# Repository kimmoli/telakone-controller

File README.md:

telakone-controller
===================

STM32F407ZG + CC3100MOD WiFi with external antenna

12V to 3.3V switch mode power supply

Full bridge motor control with current measurement

4x high-side outputs
* PWM capable
* +12V, few amps

Dual isolated eBike motor control
* Throttle control (0-5V output)
* Brake and Reverse (low-side outputs)
* +48V voltage measurement

+12V supply voltage measurement

Temperature sensor

3-Axis accelerometer

Joystick input
* 2 potentiometers
* 2 buttons

Speed sensor inputs
* 2 channels
* for MLX90217 gear tooth sensor

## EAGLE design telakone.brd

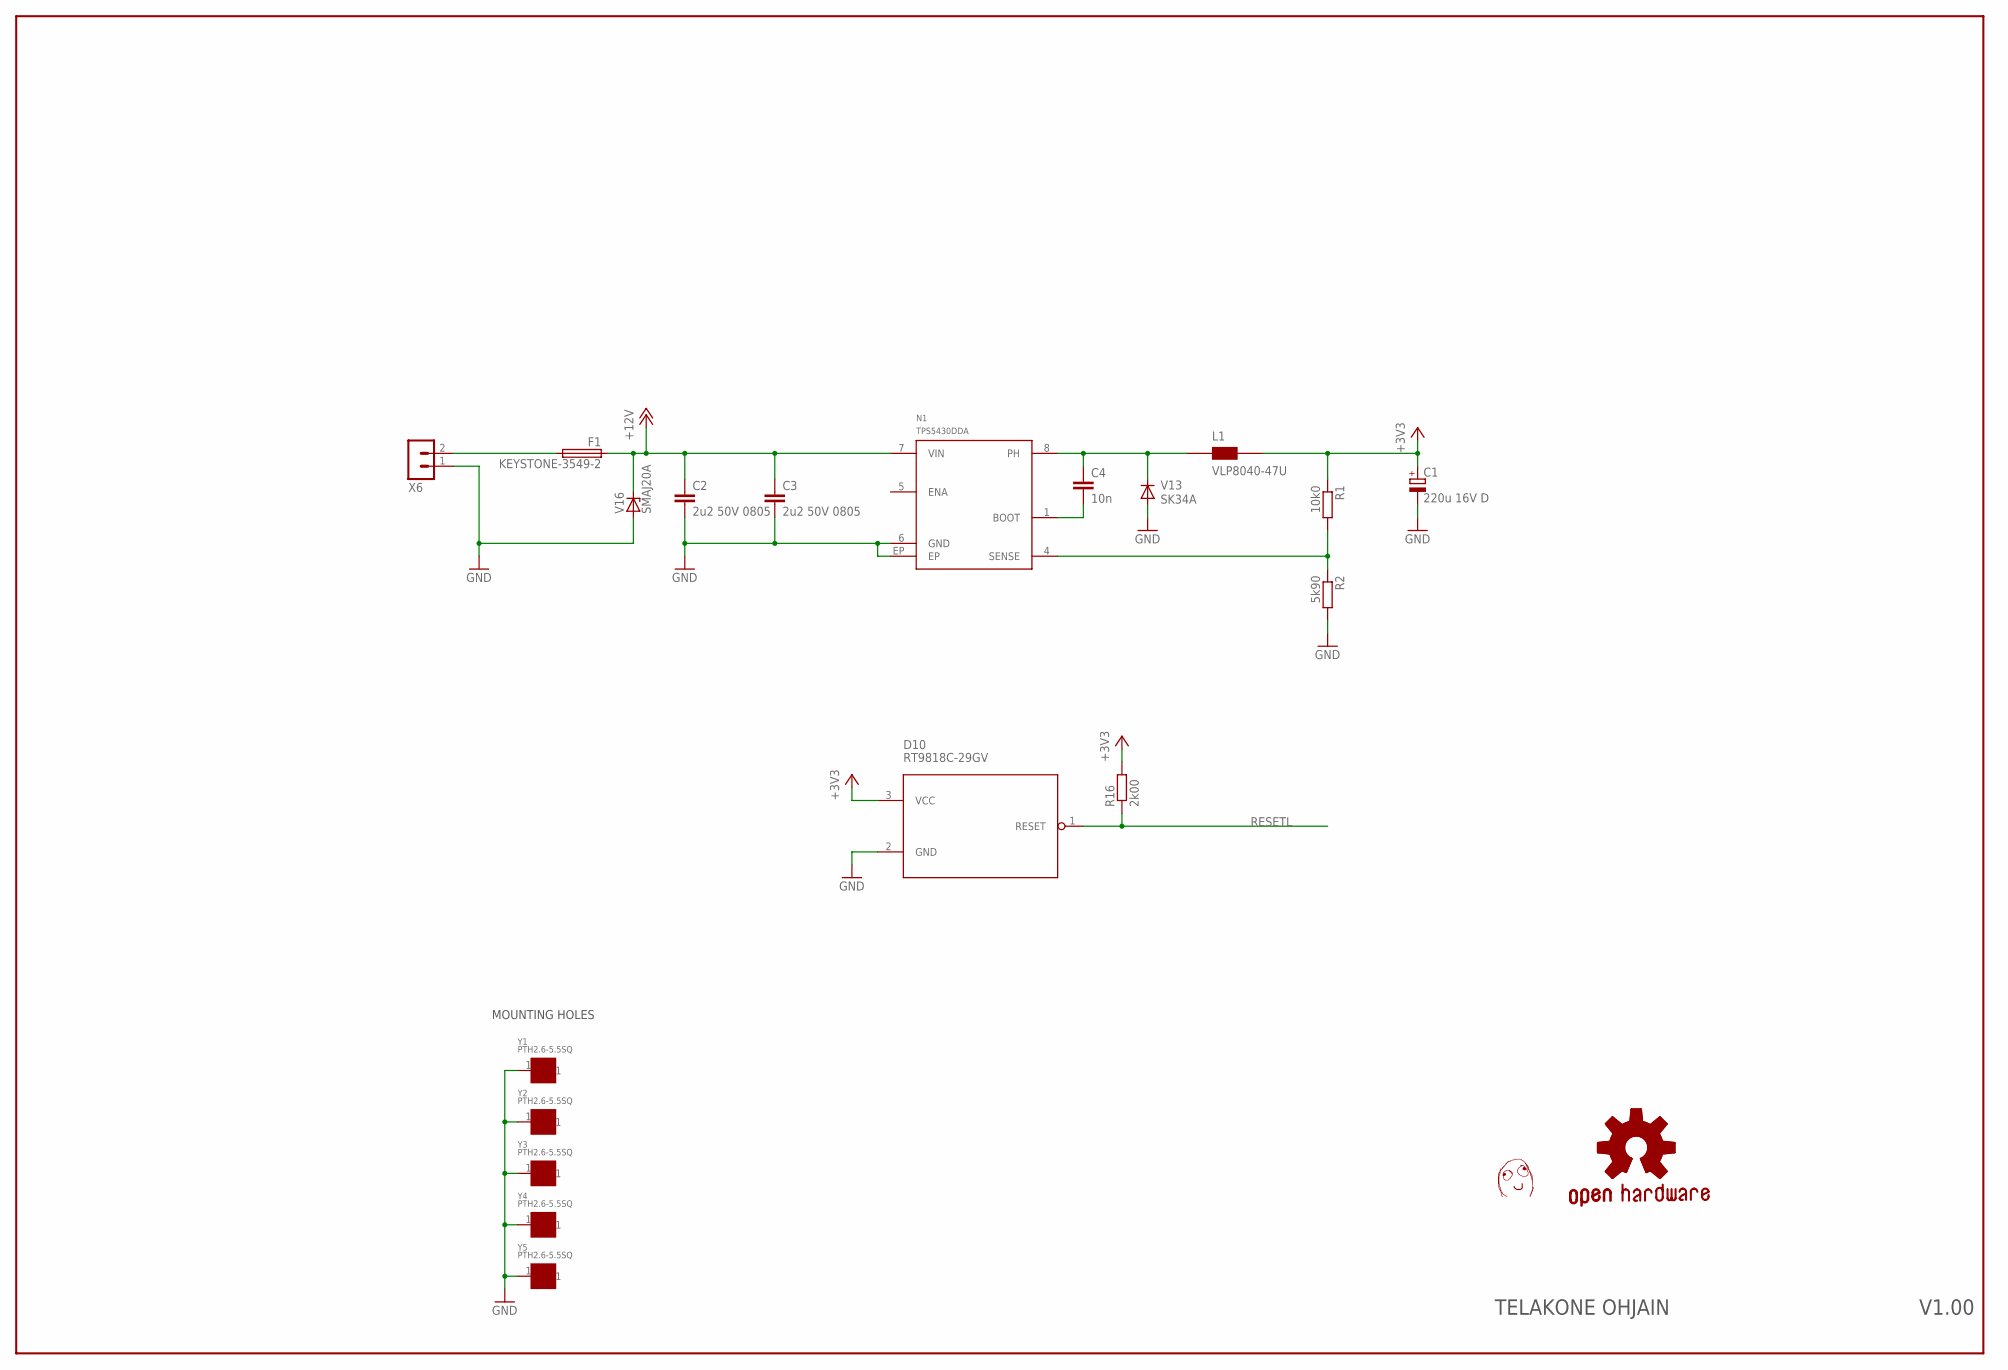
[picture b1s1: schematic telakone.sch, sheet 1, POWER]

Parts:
C1: 220u 16V D; CT7343
C2, C3: 2u2 50V 0805; C0805
C4: 10n; C0603
D10: RT9818C-29GV; SOT23
F1: KEYSTONE-3549-2
L1: VLP8040-47U; VLP8040
N1: TPS5430DDA; SOIC8-N-EP
R1: 10k0; R0603
R2: 5k90; R0603
R16: 2k00; R0603
U$1: DAFUG
V13: SK34A; DO214AC
V16: SMAJ20A; DO214AC
X6: TE_RUUVILIITIN2
Y1, Y2, Y3, Y4, Y5: PTH2.6-5.5SQ; PTH-2.6-5.5SQ

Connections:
+3V3: C1.+, D10.3 (VCC), L1.2 (B), R1.1, R16.2; also elsewhere on the board
+12V: C2.1, C3.1, F1.1, F1.4 (1), N1.7 (VIN), V16.C; also elsewhere on the board
GND: C1.-, C2.2, C3.2, D10.2 (GND), N1.6 (GND), N1.EP, R2.2, V13.A, V16.A, X6.1, Y1.1, Y2.1, Y3.1, Y4.1, Y5.1; also elsewhere on the board
unnamed: C4.1, L1.1 (A), N1.8 (PH), V13.C
unnamed: C4.2, N1.1 (BOOT)
unnamed: N1.4 (SENSE), R1.2, R2.1
unnamed: F1.2, F1.3 (2), X6.2
RESETL: D10.1 (RESET), R16.1; also elsewhere on the board

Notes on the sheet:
MOUNTING HOLES
V1.00
TELAKONE OHJAIN

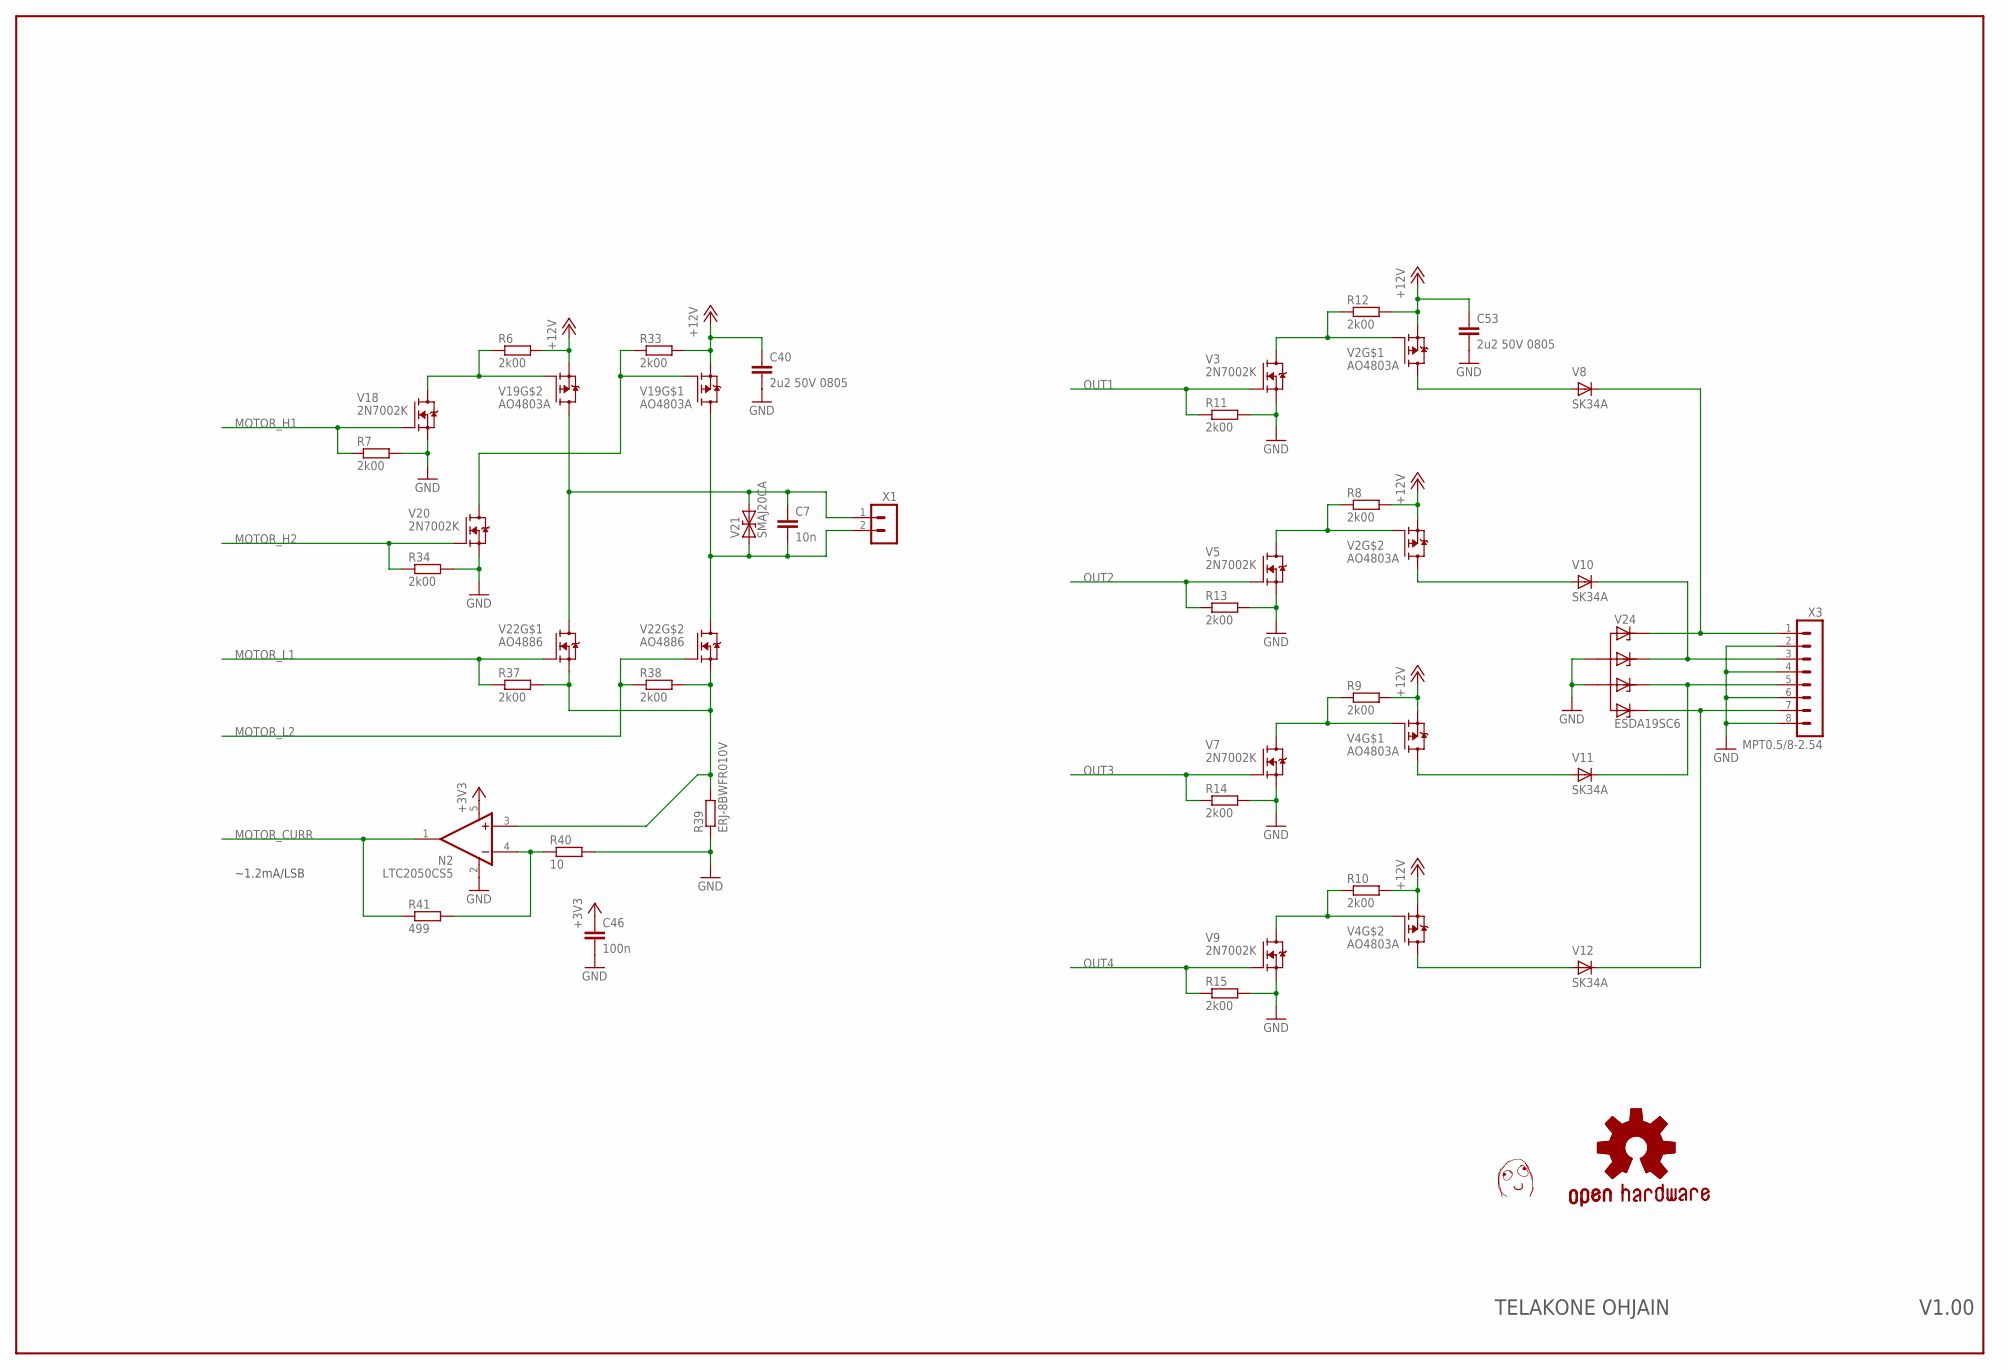
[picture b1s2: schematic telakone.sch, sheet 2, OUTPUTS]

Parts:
C7: 10n; C0603
C40, C53: 2u2 50V 0805; C0805
C46: 100n; C0603
N2: LTC2050CS5; SOT95P280X145-5N
R6, R7, R8, R9, R10, R11, R12, R13, R14, R15, R33, R34, R37, R38: 2k00; R0603
R39: ERJ-8BWFR010V; R1206
R40: 10; R0603
R41: 499; R0603
U$3: DAFUG
V2, V4, V19: AO4803A; SOIC8-N_MC
V3, V5, V7, V9, V18, V20: 2N7002K; SOT23
V8, V10, V11, V12: SK34A; DO214AC
V21: SMAJ20CA; DO214AC
V22: AO4886; SOIC8-N_MC
V24: ESDA19SC6; SOT23-6
X1: TE_RUUVILIITIN2
X3: MPT0.5/8-2.54

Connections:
+3V3: C46.1, N2.5 (V+); also elsewhere on the board
+12V: C40.1, C53.1, R6.2, R8.2, R9.2, R10.2, R12.2, R33.2, V2.1 (S), V2.3 (S), V4.1 (S), V4.3 (S), V19.1 (S), V19.3 (S); also elsewhere on the board
GND: C40.2, C46.2, C53.2, N2.2 (V-), R7.2, R11.2, R13.2, R14.2, R15.2, R34.2, R39.1, R40.2, V3.2 (S), V5.2 (S), V7.2 (S), V9.2 (S), V18.2 (S), V20.2 (S), V24.2 (A), V24.5 (A1), X3.2, X3.4, X3.6, X3.8; also elsewhere on the board
MOTOR_CURR: N2.1 (OUT), R41.1; also elsewhere on the board
MOTOR_H1: R7.1, V18.1 (G); also elsewhere on the board
MOTOR_H2: R34.1, V20.1 (G); also elsewhere on the board
MOTOR_L1: R37.1, V22.4 (G); also elsewhere on the board
MOTOR_L2: R38.1, V22.2 (G); also elsewhere on the board
unnamed: R6.1, V18.3 (D), V19.2 (G)
unnamed: R33.1, V19.4 (G), V20.3 (D)
unnamed: N2.3 (+IN), R37.2, R38.2, R39.2, V22.1 (S), V22.3 (S)
unnamed: N2.4 (-IN), R40.1, R41.2
unnamed: R8.1, V2.2 (G), V5.3 (D)
unnamed: R12.1, V2.4 (G), V3.3 (D)
unnamed: R9.1, V4.4 (G), V7.3 (D)
unnamed: R10.1, V4.2 (G), V9.3 (D)
unnamed: V12.C, V24.6 (C3), X3.7
unnamed: V11.C, V24.4 (C2), X3.5
unnamed: V10.C, V24.3 (C1), X3.3
unnamed: V8.C, V24.1 (C), X3.1
NERT: V2.5 (D), V2.6 (D), V8.A
NERT1: V2.7 (D), V2.8 (D), V10.A
NERT2: V4.5 (D), V4.6 (D), V11.A
NERT3: V4.7 (D), V4.8 (D), V12.A
NERT4: C7.1, V19.7 (D), V19.8 (D), V21.A (2), V22.5 (D), V22.6 (D), X1.1
NERT5: C7.2, V19.5 (D), V19.6 (D), V21.C (1), V22.7 (D), V22.8 (D), X1.2
OUT1: R11.1, V3.1 (G); also elsewhere on the board
OUT2: R13.1, V5.1 (G); also elsewhere on the board
OUT3: R14.1, V7.1 (G); also elsewhere on the board
OUT4: R15.1, V9.1 (G); also elsewhere on the board

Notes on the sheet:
~1.2mA/LSB
V1.00
TELAKONE OHJAIN

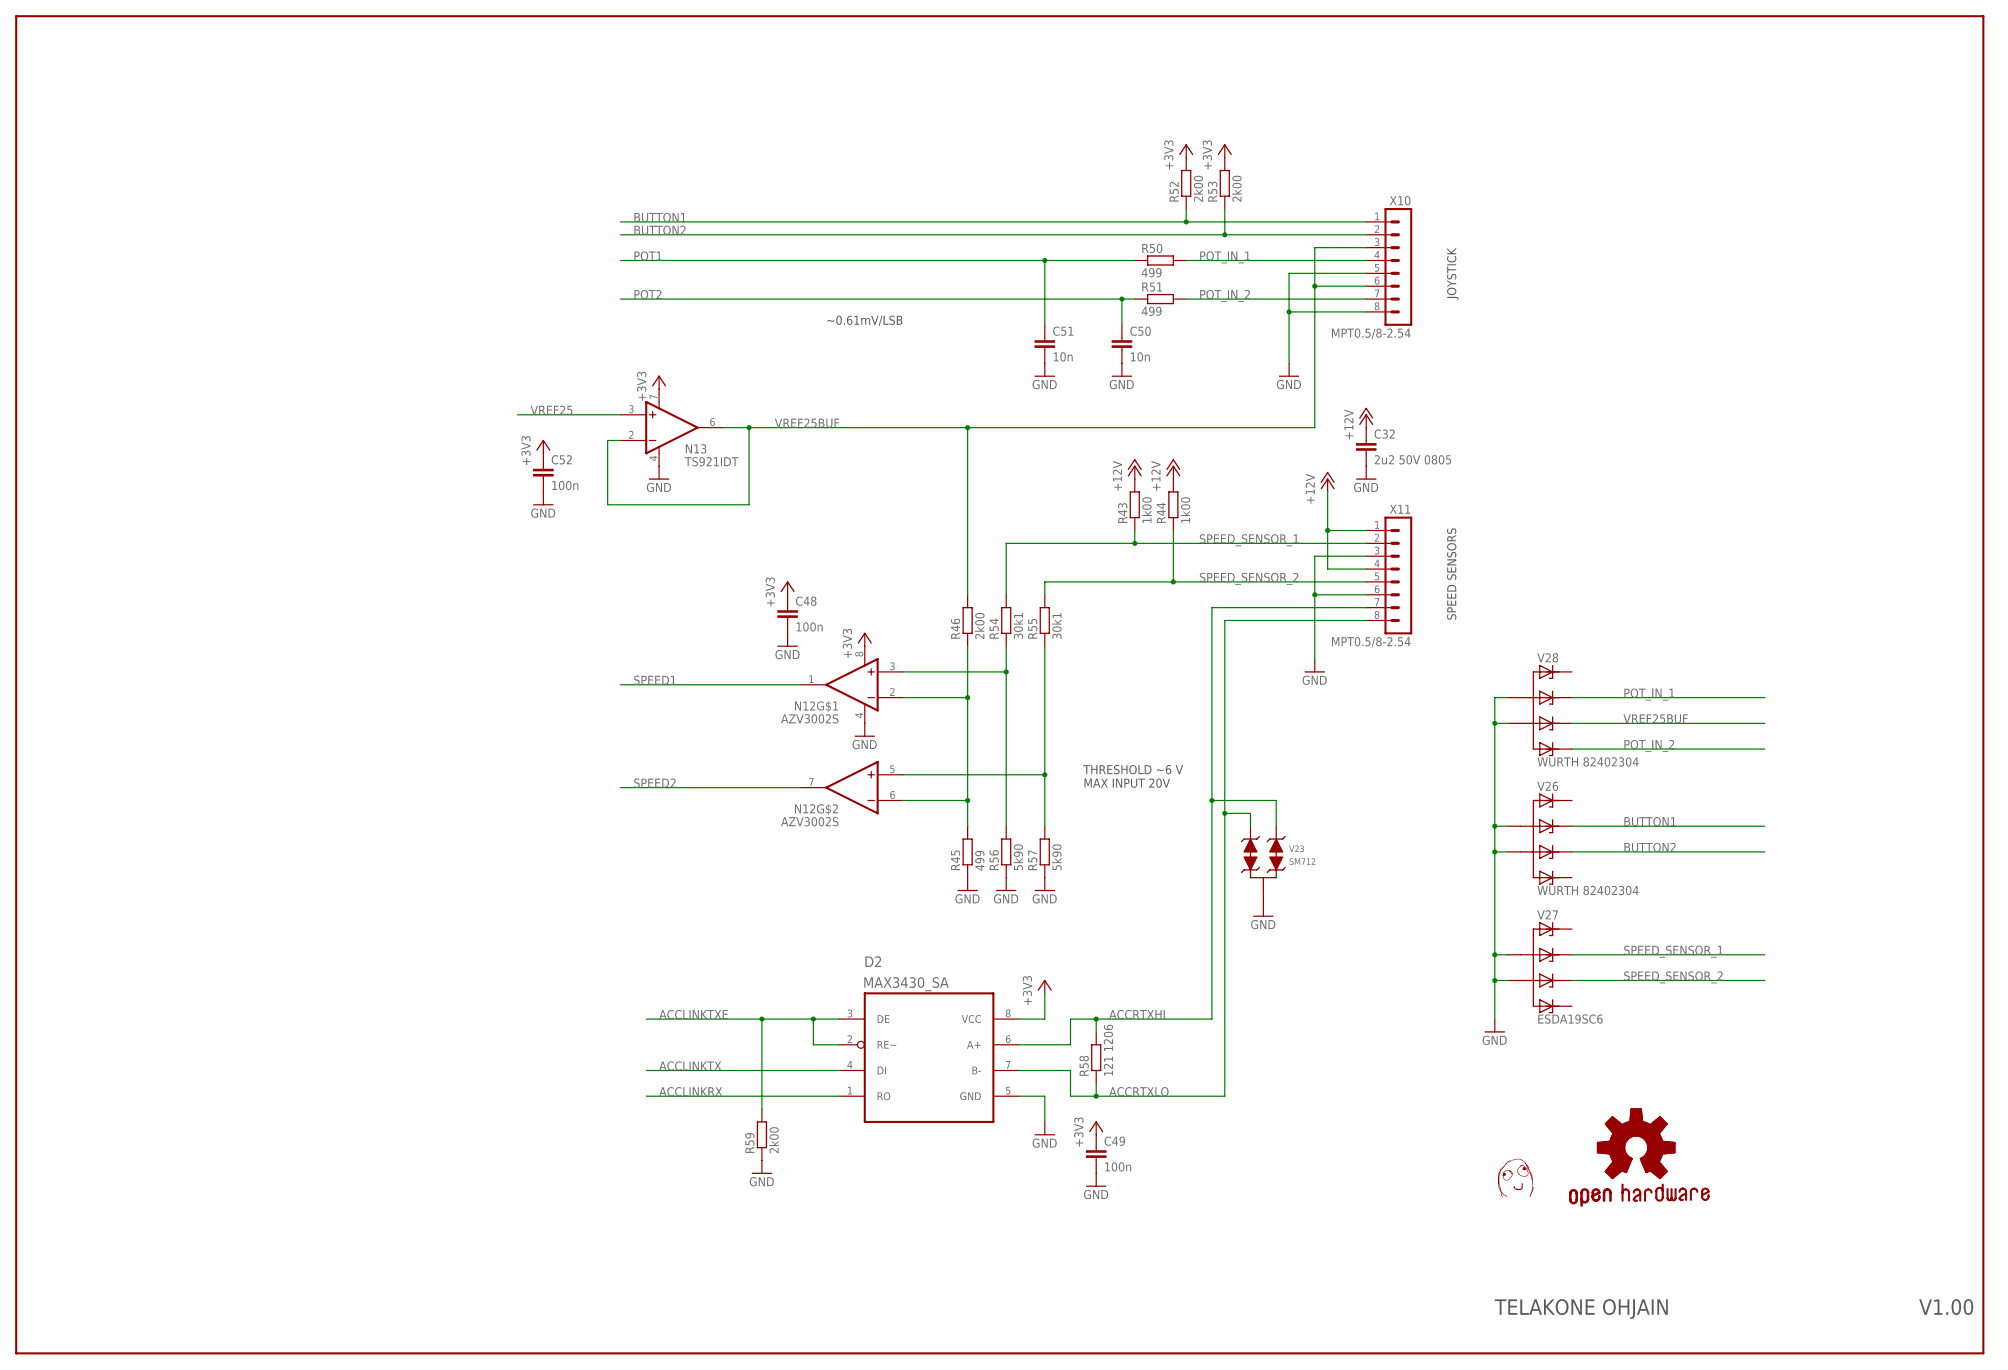
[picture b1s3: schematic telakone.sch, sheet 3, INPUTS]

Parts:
C32: 2u2 50V 0805; C0805
C48, C49, C52: 100n; C0603
C50, C51: 10n; C0603
D2: MAX3430_SA; SOIC8-N_MC
N12: AZV3002S; SOIC8-N_MC
N13: TS921IDT; SOIC8-N_MC
R43, R44: 1k00; R0603
R45, R50, R51: 499; R0603
R46, R52, R53, R59: 2k00; R0603
R54, R55: 30k1; R0603
R56, R57: 5k90; R0603
R58: 121 1206; R1206
U$5: DAFUG
V23: SM712; SOT23
V26, V28: WURTH 82402304; SOT23-6
V27: ESDA19SC6; SOT23-6
X10, X11: MPT0.5/8-2.54

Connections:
+3V3: C48.1, C49.1, C52.1, D2.8 (VCC), N12.8 (V+), N13.7 (V+), R52.2, R53.2; also elsewhere on the board
+12V: C32.1, R43.2, R44.2, X11.1, X11.4; also elsewhere on the board
ACCLINKRX: D2.1 (RO); also elsewhere on the board
ACCLINKTX: D2.4 (DI); also elsewhere on the board
ACCLINKTXE: D2.2 (RE~), D2.3 (DE), R59.2; also elsewhere on the board
ACCRTXHI: D2.6 (A+), R58.2, V23.1, X11.7
ACCRTXLO: D2.7 (B-), R58.1, V23.2, X11.8
BUTTON1: R52.1, V26.3 (C1), X10.1; also elsewhere on the board
BUTTON2: R53.1, V26.4 (C2), X10.2; also elsewhere on the board
GND: C32.2, C48.2, C49.2, C50.2, C51.2, C52.2, D2.5 (GND), N12.4 (V-), N13.4 (V-), R45.1, R56.1, R57.1, R59.1, V23.3, V26.2 (A), V26.5 (A1), V27.2 (A), V27.5 (A1), V28.2 (A), V28.5 (A1), X10.5, X10.8, X11.3, X11.6; also elsewhere on the board
unnamed: N12.3 (+IN), R54.1, R56.2
unnamed: N12.5 (+IN), R55.1, R57.2
unnamed: N12.2 (-IN), N12.6 (-IN), R45.2, R46.1
POT1: C51.1, R50.1; also elsewhere on the board
POT2: C50.1, R51.1; also elsewhere on the board
POT_IN_1: R50.2, V28.3 (C1), X10.4
POT_IN_2: R51.2, V28.6 (C3), X10.7
SPEED1: N12.1 (OUT); also elsewhere on the board
SPEED2: N12.7 (OUT); also elsewhere on the board
SPEED_SENSOR_1: R43.1, R54.2, V27.3 (C1), X11.2
SPEED_SENSOR_2: R44.1, R55.2, V27.4 (C2), X11.5
VREF25: N13.3 (+IN); also elsewhere on the board
VREF25BUF: N13.2 (-IN), N13.6 (OUT), R46.2, V28.4 (C2), X10.3, X10.6

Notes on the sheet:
JOYSTICK
~0.61mV/LSB
THRESHOLD ~6 V MAX INPUT 20V
SPEED SENSORS
V1.00
TELAKONE OHJAIN

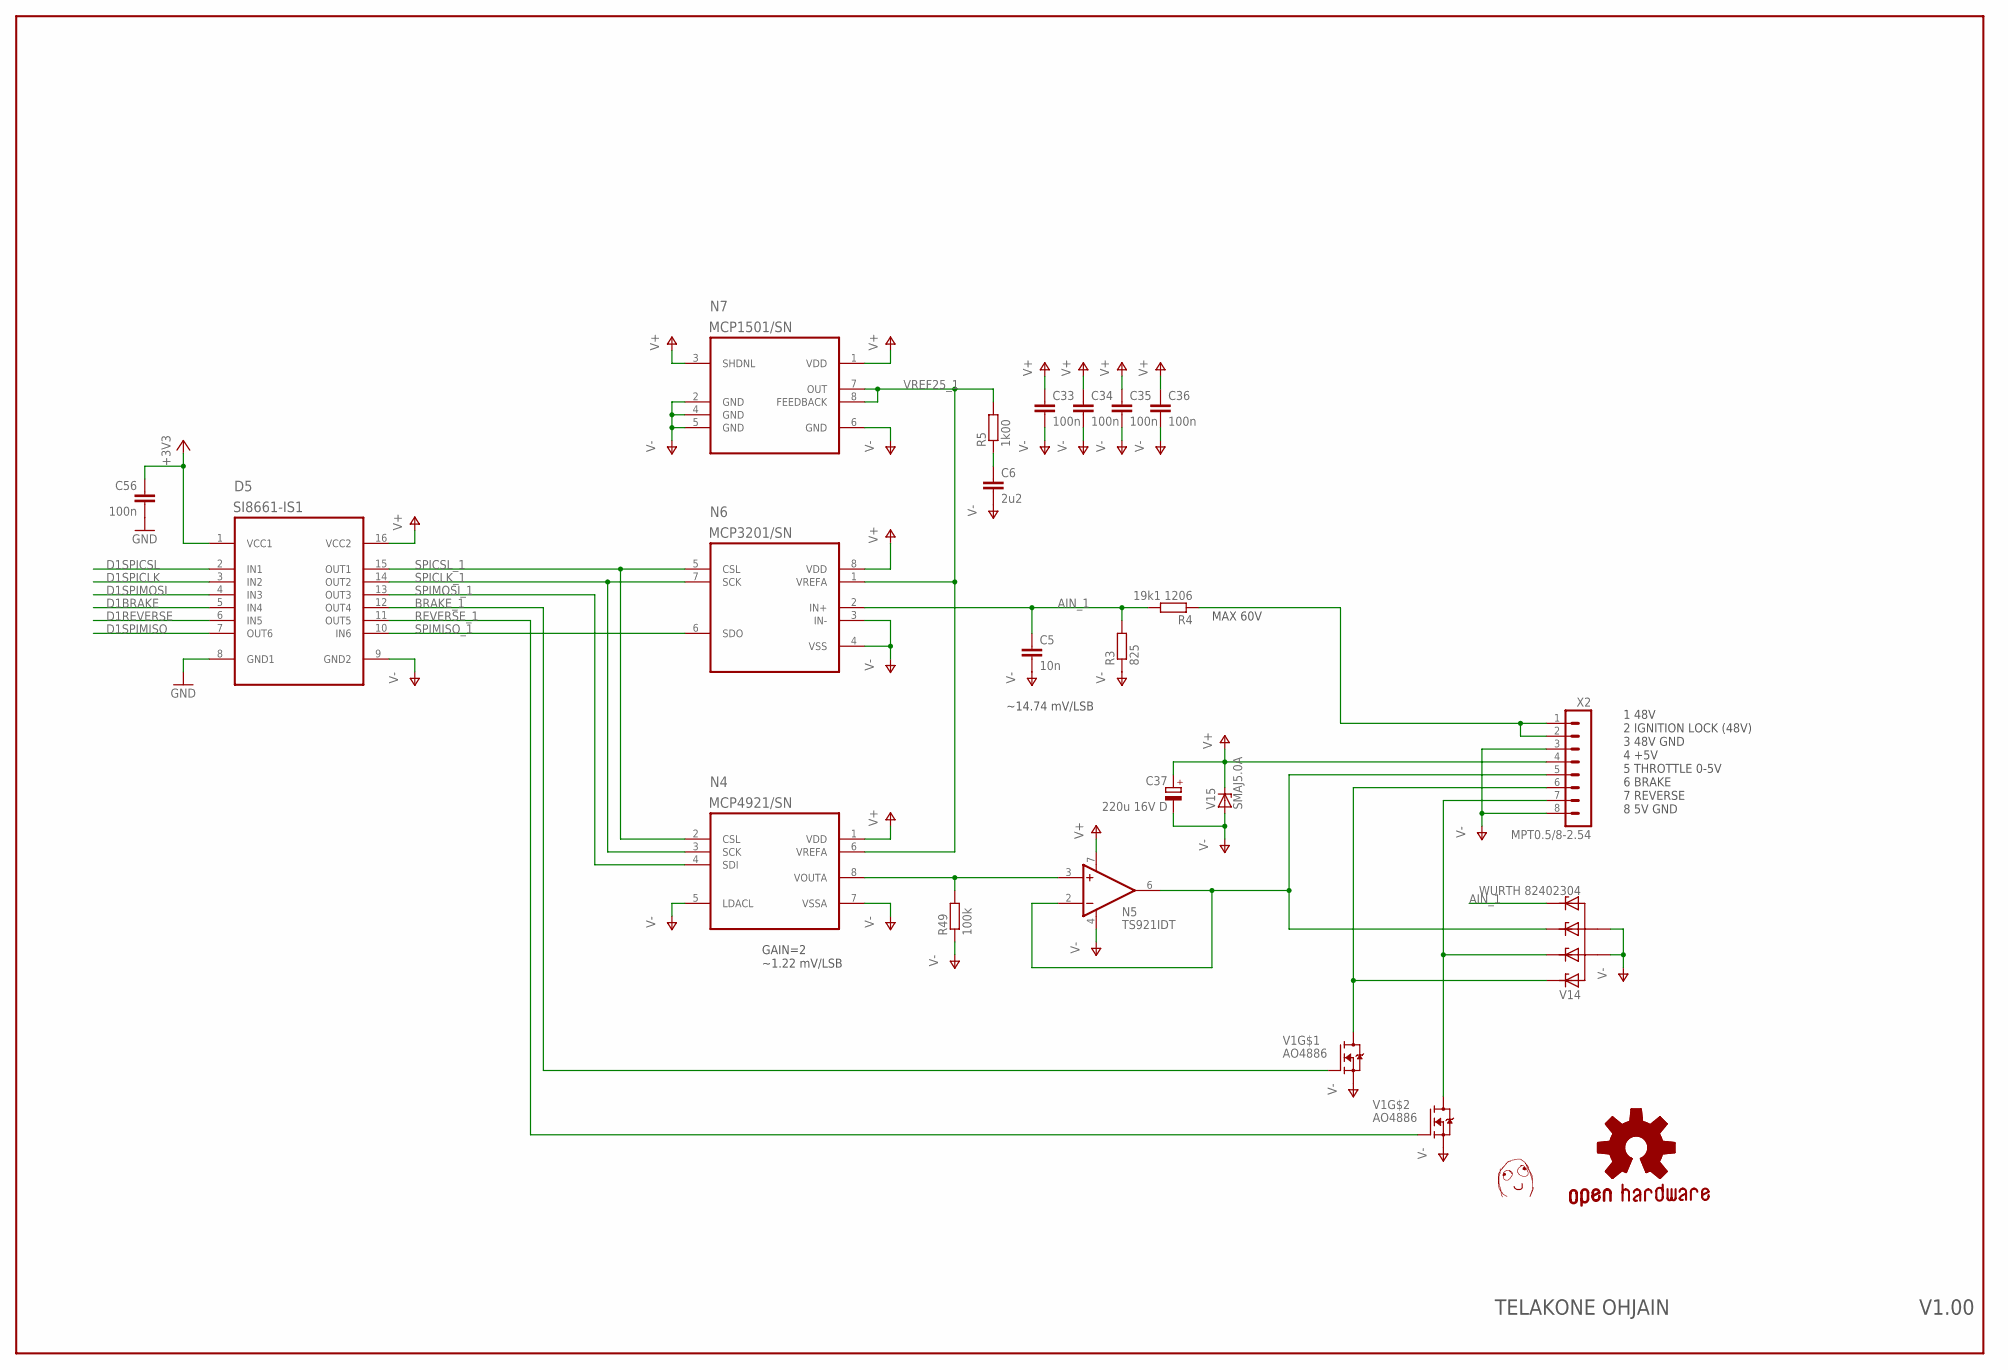
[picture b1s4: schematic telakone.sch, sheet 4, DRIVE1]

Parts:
C5: 10n; C0603
C6: 2u2; C0603
C33, C34, C35, C36, C56: 100n; C0603
C37: 220u 16V D; CT7343
D5: SI8661-IS1; SOIC16-N
N4: MCP4921/SN; SOIC8-N_MC
N5: TS921IDT; SOIC8-N_MC
N6: MCP3201/SN; SOIC8-N_MC
N7: MCP1501/SN; SOIC8-N_MC
R3: 825; R0603
R4: 19k1 1206; R1206
R5: 1k00; R0603
R49: 100k; R0603
U$7: DAFUG
V1: AO4886; SOIC8-N_MC
V14: WURTH 82402304; SOT23-6
V15: SMAJ5.0A; DO214AC
X2: MPT0.5/8-2.54

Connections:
+3V3: C56.1, D5.1 (VCC1); also elsewhere on the board
+48V_1: R4.1, X2.1, X2.2
AIN_1: C5.1, N6.2 (IN+), R3.2, R4.2, V14.6 (C3)
BRAKE_1: D5.12 (OUT4), V1.4 (G)
BRAKE_OD_1: V1.5 (D), V1.6 (D), V14.1 (C), X2.6
D1BRAKE: D5.5 (IN4); also elsewhere on the board
D1REVERSE: D5.6 (IN5); also elsewhere on the board
D1SPICLK: D5.3 (IN2); also elsewhere on the board
D1SPICSL: D5.2 (IN1); also elsewhere on the board
D1SPIMISO: D5.7 (OUT6); also elsewhere on the board
D1SPIMOSI: D5.4 (IN3); also elsewhere on the board
GND: C56.2, D5.8 (GND1); also elsewhere on the board
unnamed: C6.1, R5.1
REVERSE_1: D5.11 (OUT5), V1.2 (G)
REVERSE_OD_1: V1.7 (D), V1.8 (D), V14.3 (C1), X2.7
SPICLK_1: D5.14 (OUT2), N4.3 (SCK), N6.7 (SCK)
SPICSL_1: D5.15 (OUT1), N4.2 (CSL), N6.5 (CSL)
SPIMISO_1: D5.10 (IN6), N6.6 (SDO)
SPIMOSI_1: D5.13 (OUT3), N4.4 (SDI)
THROTTLE_1: N4.8 (VOUTA), N5.3 (+IN), R49.2
THROTTLE_BUFFERED_1: N5.2 (-IN), N5.6 (OUT), V14.4 (C2), X2.5
V+1: C33.1, C34.1, C35.1, C36.1, C37.+, D5.16 (VCC2), N4.1 (VDD), N5.7 (V+), N6.8 (VDD), N7.1 (VDD), N7.3 (SHDNL), V15.C, X2.4
V-1: C5.2, C6.2, C33.2, C34.2, C35.2, C36.2, C37.-, D5.9 (GND2), N4.5 (LDACL), N4.7 (VSSA), N5.4 (V-), N6.3 (IN-), N6.4 (VSS), N7.2 (GND), N7.4 (GND), N7.5 (GND), N7.6 (GND), R3.1, R49.1, V1.1 (S), V1.3 (S), V14.2 (A), V14.5 (A1), V15.A, X2.3, X2.8
VREF25_1: N4.6 (VREFA), N6.1 (VREFA), N7.7 (OUT), N7.8 (FEEDBACK), R5.2

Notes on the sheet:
1 48V 2 IGNITION LOCK (48V) 3 48V GND 4 +5V 5 THROTTLE 0-5V 6 BRAKE 7 REVERSE 8 5V GND
MAX 60V
~14.74 mV/LSB
GAIN=2 ~1.22 mV/LSB
V1.00
TELAKONE OHJAIN

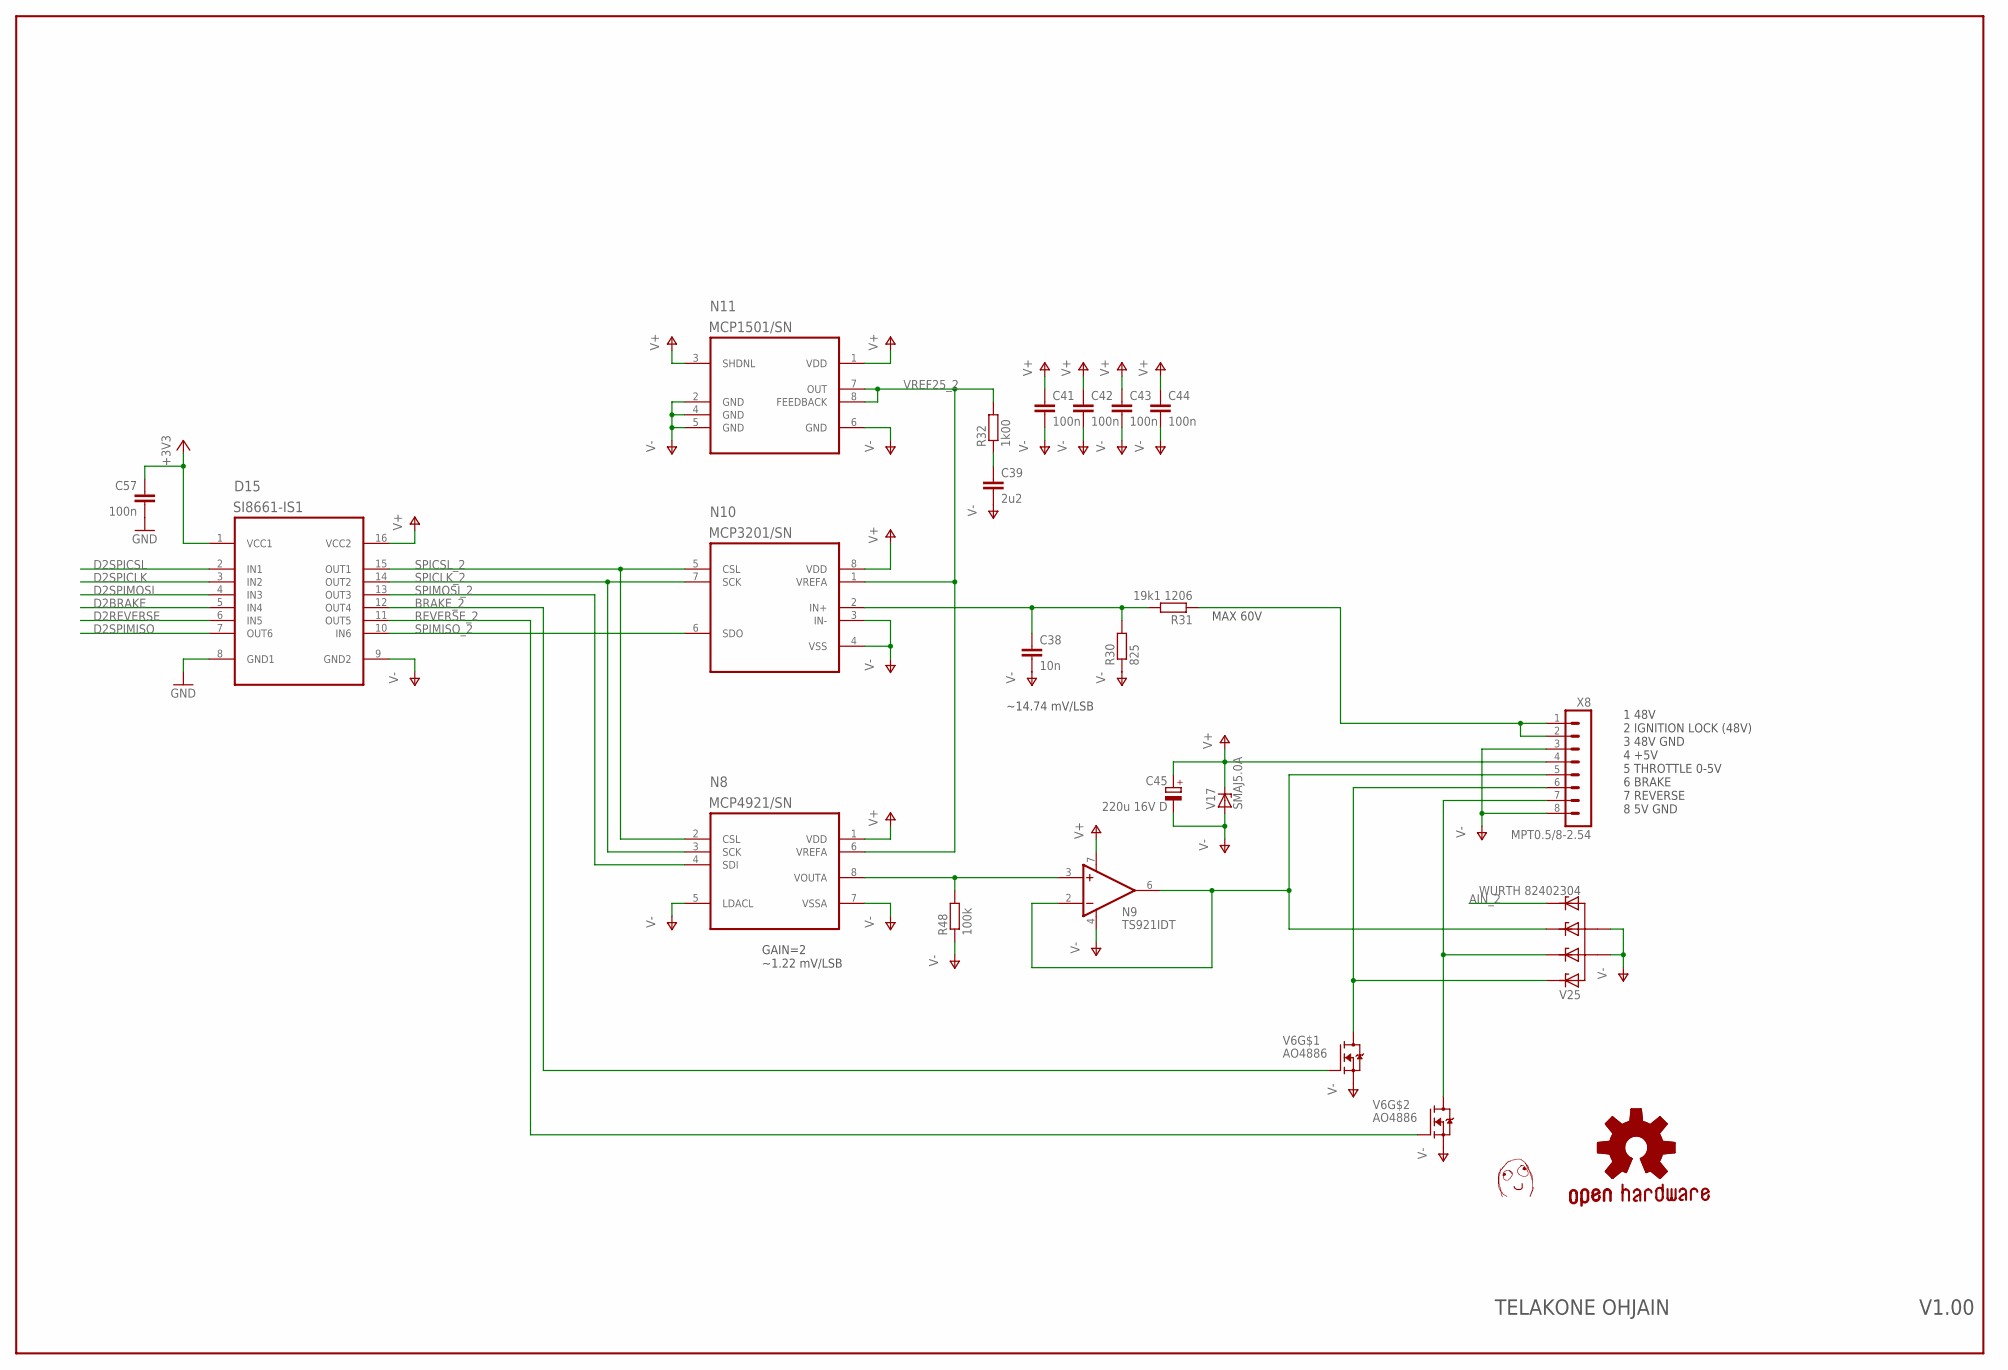
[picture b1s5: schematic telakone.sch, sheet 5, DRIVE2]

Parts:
C38: 10n; C0603
C39: 2u2; C0603
C41, C42, C43, C44, C57: 100n; C0603
C45: 220u 16V D; CT7343
D15: SI8661-IS1; SOIC16-N
N8: MCP4921/SN; SOIC8-N_MC
N9: TS921IDT; SOIC8-N_MC
N10: MCP3201/SN; SOIC8-N_MC
N11: MCP1501/SN; SOIC8-N_MC
R30: 825; R0603
R31: 19k1 1206; R1206
R32: 1k00; R0603
R48: 100k; R0603
U$9: DAFUG
V6: AO4886; SOIC8-N_MC
V17: SMAJ5.0A; DO214AC
V25: WURTH 82402304; SOT23-6
X8: MPT0.5/8-2.54

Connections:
+3V3: C57.1, D15.1 (VCC1); also elsewhere on the board
+48V_2: R31.1, X8.1, X8.2
AIN_2: C38.1, N10.2 (IN+), R30.2, R31.2, V25.6 (C3)
BRAKE_2: D15.12 (OUT4), V6.4 (G)
BRAKE_OD_2: V6.5 (D), V6.6 (D), V25.1 (C), X8.6
D2BRAKE: D15.5 (IN4); also elsewhere on the board
D2REVERSE: D15.6 (IN5); also elsewhere on the board
D2SPICLK: D15.3 (IN2); also elsewhere on the board
D2SPICSL: D15.2 (IN1); also elsewhere on the board
D2SPIMISO: D15.7 (OUT6); also elsewhere on the board
D2SPIMOSI: D15.4 (IN3); also elsewhere on the board
GND: C57.2, D15.8 (GND1); also elsewhere on the board
unnamed: C39.1, R32.1
REVERSE_2: D15.11 (OUT5), V6.2 (G)
REVERSE_OD_2: V6.7 (D), V6.8 (D), V25.3 (C1), X8.7
SPICLK_2: D15.14 (OUT2), N8.3 (SCK), N10.7 (SCK)
SPICSL_2: D15.15 (OUT1), N8.2 (CSL), N10.5 (CSL)
SPIMISO_2: D15.10 (IN6), N10.6 (SDO)
SPIMOSI_2: D15.13 (OUT3), N8.4 (SDI)
THROTTLE_2: N8.8 (VOUTA), N9.3 (+IN), R48.2
THROTTLE_BUFFERED_2: N9.2 (-IN), N9.6 (OUT), V25.4 (C2), X8.5
V+2: C41.1, C42.1, C43.1, C44.1, C45.+, D15.16 (VCC2), N8.1 (VDD), N9.7 (V+), N10.8 (VDD), N11.1 (VDD), N11.3 (SHDNL), V17.C, X8.4
V-2: C38.2, C39.2, C41.2, C42.2, C43.2, C44.2, C45.-, D15.9 (GND2), N8.5 (LDACL), N8.7 (VSSA), N9.4 (V-), N10.3 (IN-), N10.4 (VSS), N11.2 (GND), N11.4 (GND), N11.5 (GND), N11.6 (GND), R30.1, R48.1, V6.1 (S), V6.3 (S), V17.A, V25.2 (A), V25.5 (A1), X8.3, X8.8
VREF25_2: N8.6 (VREFA), N10.1 (VREFA), N11.7 (OUT), N11.8 (FEEDBACK), R32.2

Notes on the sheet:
1 48V 2 IGNITION LOCK (48V) 3 48V GND 4 +5V 5 THROTTLE 0-5V 6 BRAKE 7 REVERSE 8 5V GND
MAX 60V
~14.74 mV/LSB
GAIN=2 ~1.22 mV/LSB
V1.00
TELAKONE OHJAIN

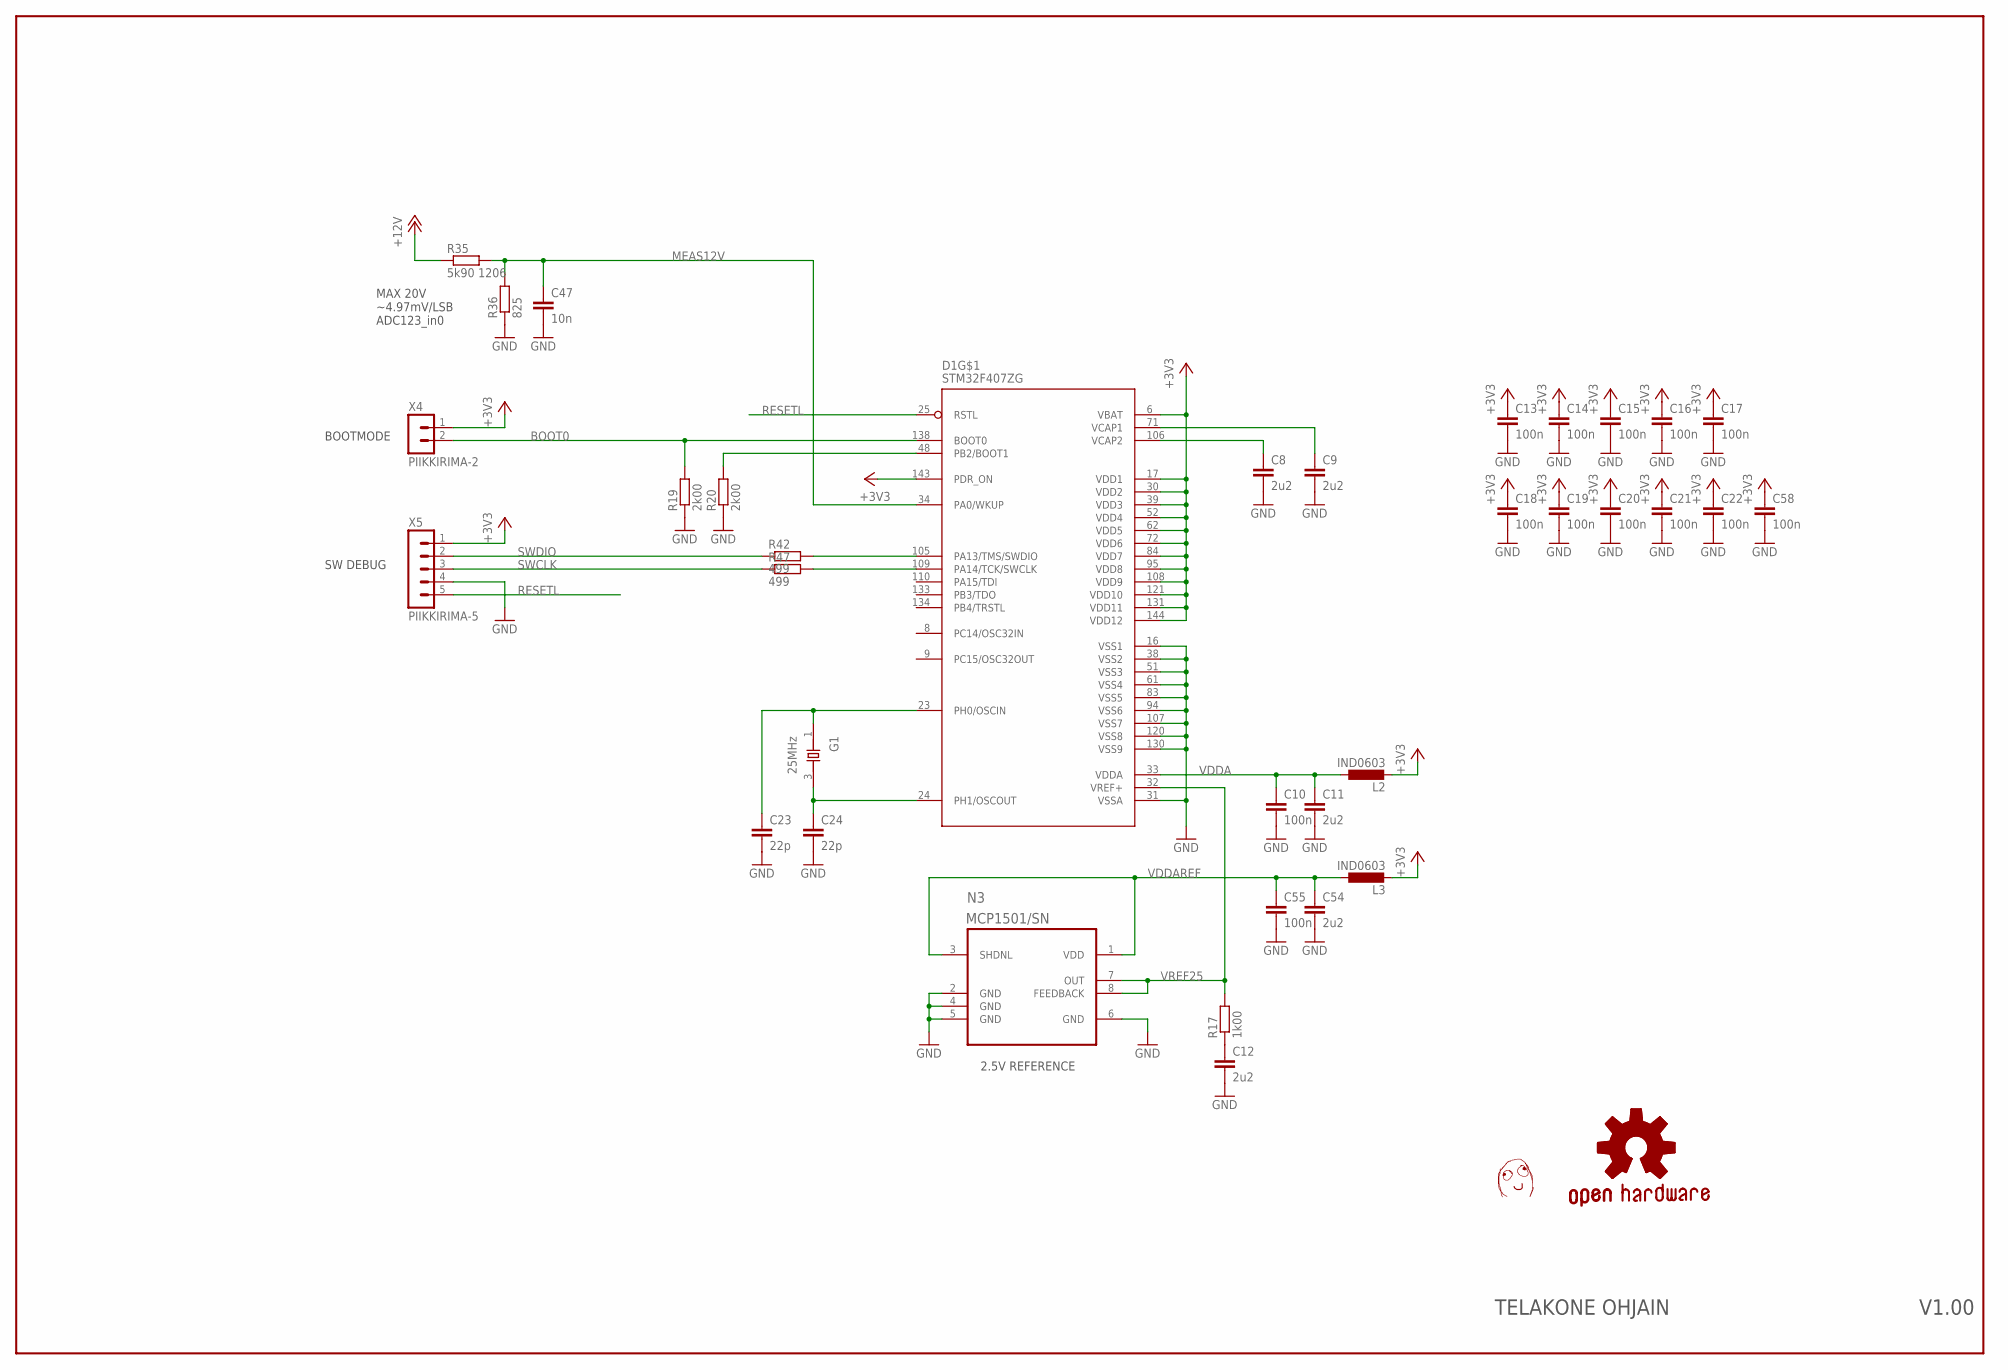
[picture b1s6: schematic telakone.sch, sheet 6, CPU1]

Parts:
C8, C9, C11, C12, C54: 2u2; C0603
C10, C13, C14, C15, C16, C17, C18, C19, C20, C21, C22, C55, C58: 100n; C0603
C23, C24: 22p; C0603
C47: 10n; C0603
D1: STM32F407ZG; LQFP-144
G1: 25MHz; X_3225
L2, L3: IND0603; R0603
N3: MCP1501/SN; SOIC8-N_MC
R17: 1k00; R0603
R19, R20: 2k00; R0603
R35: 5k90 1206; R1206
R36: 825; R0603
R42, R47: 499; R0603
U$11: DAFUG
X4: PIIKKIRIMA-2
X5: PIIKKIRIMA-5

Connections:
+3V3: C13.1, C14.1, C15.1, C16.1, C17.1, C18.1, C19.1, C20.1, C21.1, C22.1, C58.1, D1.6 (VBAT), D1.17 (VDD1), D1.30 (VDD2), D1.39 (VDD3), D1.52 (VDD4), D1.62 (VDD5), D1.72 (VDD6), D1.84 (VDD7), D1.95 (VDD8), D1.108 (VDD9), D1.121 (VDD10), D1.131 (VDD11), D1.143 (PDR_ON), D1.144 (VDD12), L2.2, L3.2, X4.1, X5.1; also elsewhere on the board
+12V: R35.1; also elsewhere on the board
BOOT0: D1.138 (BOOT0), R19.2, X4.2
GND: C8.2, C9.2, C10.2, C11.2, C12.2, C13.2, C14.2, C15.2, C16.2, C17.2, C18.2, C19.2, C20.2, C21.2, C22.2, C23.2, C24.2, C47.2, C54.2, C55.2, C58.2, D1.16 (VSS1), D1.31 (VSSA), D1.38 (VSS2), D1.51 (VSS3), D1.61 (VSS4), D1.83 (VSS5), D1.94 (VSS6), D1.107 (VSS7), D1.120 (VSS8), D1.130 (VSS9), N3.2 (GND), N3.4 (GND), N3.5 (GND), N3.6 (GND), R19.1, R20.1, R36.1, X5.4; also elsewhere on the board
MEAS12V: C47.1, D1.34 (PA0/WKUP), R35.2, R36.2
unnamed: D1.109 (PA14/TCK/SWCLK), R47.2
unnamed: D1.105 (PA13/TMS/SWDIO), R42.2
unnamed: C12.1, R17.1
unnamed: D1.48 (PB2/BOOT1), R20.2
OSCIN: C23.1, D1.23 (PH0/OSCIN), G1.1 (X1)
OSCOUT: C24.1, D1.24 (PH1/OSCOUT), G1.3 (X2)
RESETL: D1.25 (RSTL), X5.5; also elsewhere on the board
SWCLK: R47.1, X5.3
SWDIO: R42.1, X5.2
VCAP1: C9.1, D1.71 (VCAP1)
VCAP2: C8.1, D1.106 (VCAP2)
VDDA: C10.1, C11.1, D1.33 (VDDA), L2.1
VDDAREF: C54.1, C55.1, L3.1, N3.1 (VDD), N3.3 (SHDNL)
VREF25: D1.32 (VREF+), N3.7 (OUT), N3.8 (FEEDBACK), R17.2; also elsewhere on the board

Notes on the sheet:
2.5V REFERENCE
SW DEBUG
BOOTMODE
MAX 20V ~4.97mV/LSB ADC123_in0
V1.00
TELAKONE OHJAIN
